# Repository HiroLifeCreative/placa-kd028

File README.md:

# Placa KD028 v1.0 — Proyecto KiCad (INICIO, no fabricación)

Abrir en KiCad 8: `placa-kd028.kicad_pro` (o abrir `placa-kd028.kicad_pcb` y
`placa-kd028.kicad_sch` desde KiCad).

Contenido:
- Esquemático v1.0: U1 ESP32-S3-WROOM-1-N8R8, U2 buck 5V->3.3V 3A,
  U3 boost LED ~17.5V, J1 FPC 40 pines ST7701S, U5 BH1750, U6 TMP117,
  USB, ESD, BOOT/RESET. Conexiones por etiquetas globales de red.
- PCB: contorno redondo Ø70 mm (Edge.Cuts), 1.2 mm, 4 capas
  (F.Cu, In1.Cu, In2.Cu, B.Cu), huellas colocadas según el layout v1.0,
  pistas iniciales RGB (0.25 mm), alimentación 1.5 mm y LED 1.0 mm,
  3 agujeros M3 Ø3.2 mm a radio 31 mm.

Pasos en KiCad:
1. Schematic Editor: Tools > Electrical Rules Check (ERC) — corregir
   pines sin conectar.
2. PCB Editor: Tools > Design Rules Check (DRC), y comprobar
   ancho de pista de alimentación y separación del boost.
3. Vista 3D (Alt+3) para revisar altura de componentes por detrás.

BLOQUEO ANTES DE FABRICAR (no saltar):
- Confirmar hoja de datos / plano del KD028WXFPD075: pinout exacto
  del FPC de 40 pines y cadena de LEDs. El J1 de este proyecto usa
  el pinout genérico ST7701S de la familia; si el KD028 difiere,
  hay que corregir J1 y el ruteo RGB/SPI antes de generar Gerbers.
- Medir en el coche: distancia entre centros de los 2 agujeros del
  emblema, diámetros y grosor de tapa (para la placa trasera, no
  para esta PCB, que ya es Ø70 mm).
- Solo entonces: File > Fabrication Outputs > Gerbers + Drill,
  y revisión DFM del fabricante.

Nada comprado ni fabricado con este proyecto todavía.

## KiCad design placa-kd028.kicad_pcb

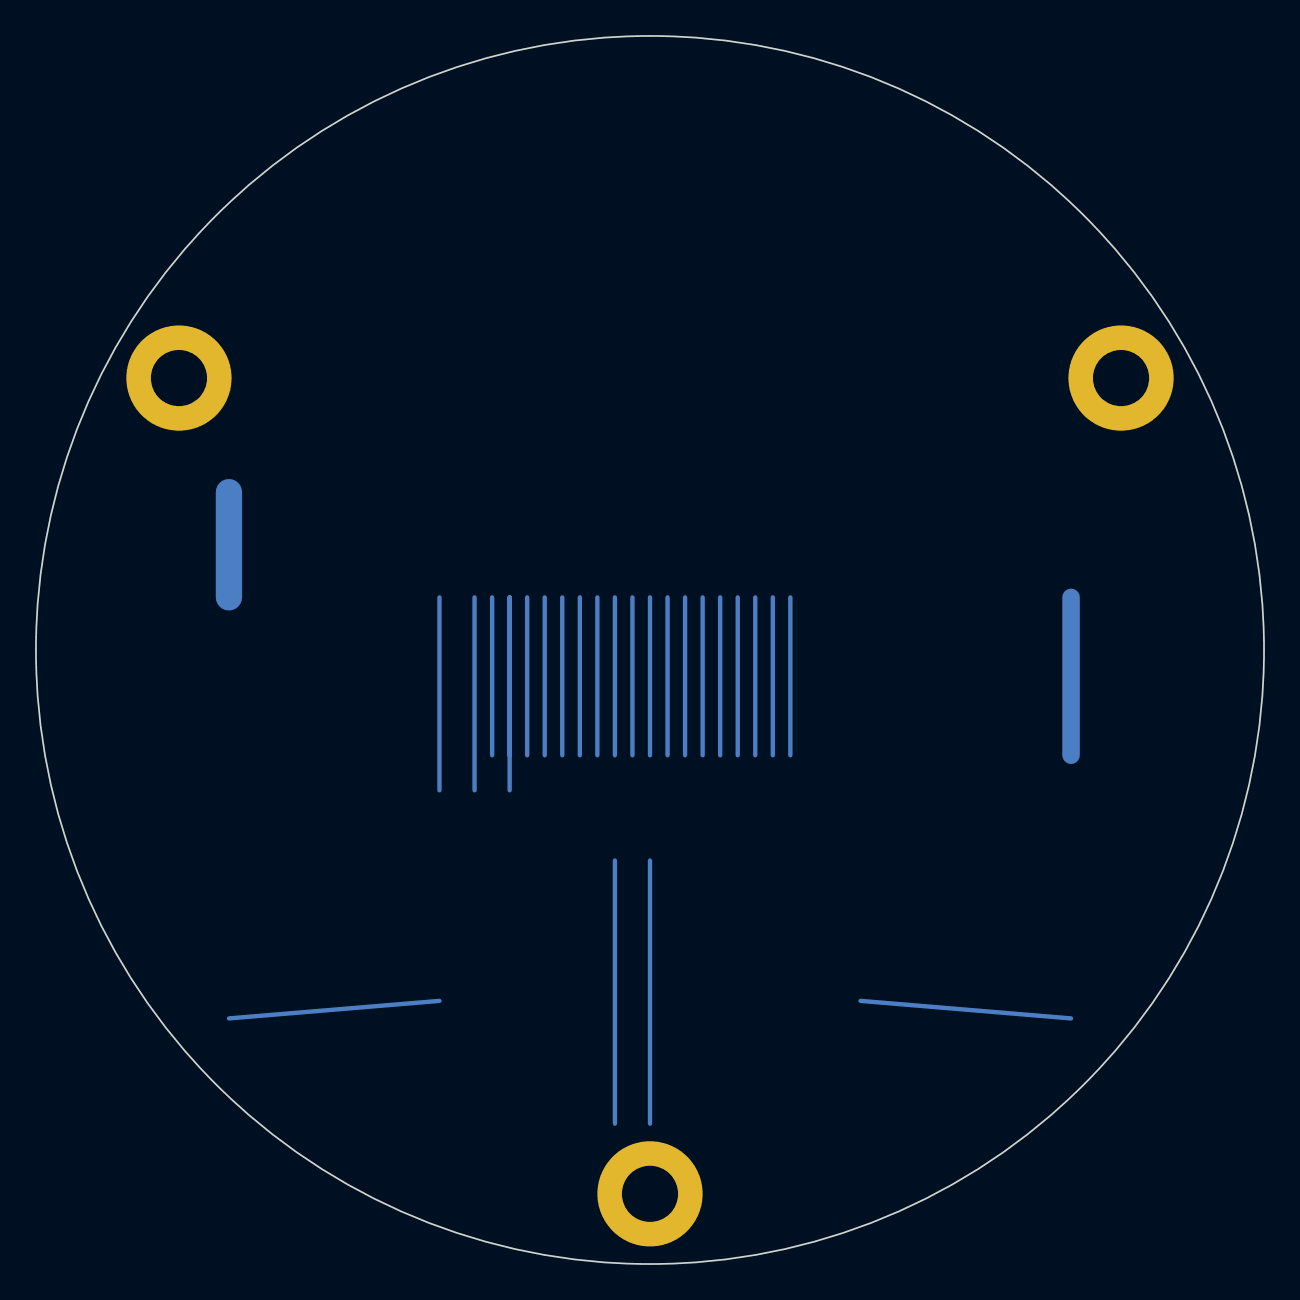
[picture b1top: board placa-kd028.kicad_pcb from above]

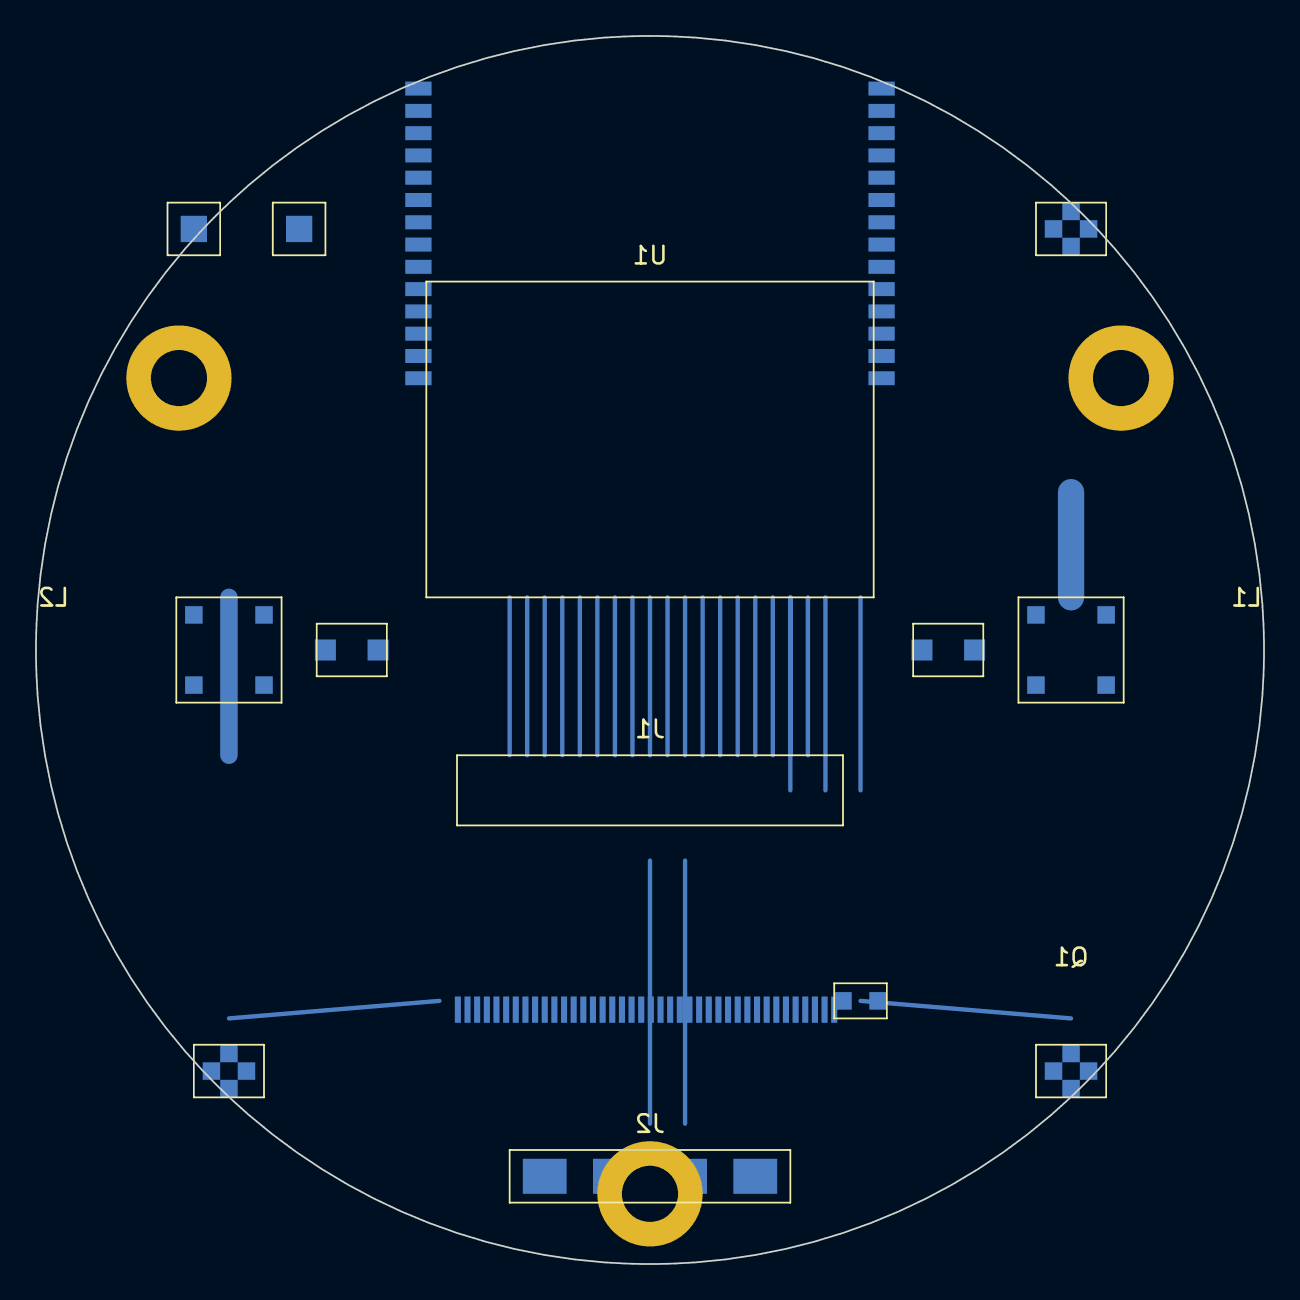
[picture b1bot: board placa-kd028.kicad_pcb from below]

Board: 4 copper layers, 70.0 x 70.0 mm, 16 parts (13 on the bottom side), 28 nets.

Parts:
H1, H2, H3: MountingHole
J1: FPC-40-0.5mm-ST7701S
J2: USB-PADS
L1: IND-2.2uH
L2: IND-BOOST
Q1: MOSFET-PANEL-EN
SW1: BOOT
SW2: RESET
U1: ESP32-S3-WROOM-1-N8R8
U2: MP2315S-BUCK-3A
U3: TPS61165-BOOST-LED
U4: USBLC6-2-ESD
U5: BH1750
U6: TMP117

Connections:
GND: H1.1, H2.1, H3.1, J1.3, J1.27, J1.28, J1.29, J1.30, J1.31, J1.32, J1.33, J1.34, J1.35, J1.36, J1.37, J1.38, J1.39, J1.40, J2.4, SW1.1, SW2.1, U1.1, U1.6, U1.11, U2.3, U3.3, U4.3, U5.4, U6.4
I2C_SCL: U1.10, U5.3, U6.3
I2C_SDA: U1.9, U5.2, U6.2
LED_PLUS: J1.1, L2.2, U3.2
PANEL_EN: Q1.2, U1.13
PANEL_RESET: J1.5, U1.12
RGB_B1: J1.10, U1.2
RGB_B2: J1.11, U1.15
RGB_B3: J1.12, U1.16
RGB_B4: J1.13, U1.17
RGB_B5: J1.14, U1.18
RGB_G0: J1.15, U1.3
RGB_G1: J1.16, U1.19
RGB_G2: J1.17, U1.20
RGB_G3: J1.18, U1.21
RGB_G4: J1.19, U1.22
RGB_G5: J1.20, U1.23
RGB_R0: J1.21, U1.24
RGB_R1: J1.22, U1.25
RGB_R2: J1.23, U1.26
RGB_R3: J1.24, U1.27
RGB_R4: J1.25, U1.28
SPI_CS: J1.8, U1.4
SPI_SCL: J1.7, U1.5
USB_DM: J2.2, U1.7, U4.1
USB_DP: J2.3, U1.8, U4.2
V3V3: J1.4, L1.1, L1.2, Q1.1, U1.14, U2.2, U2.4, U5.1, U6.1
VBUS_5V: J2.1, L2.1, U2.1, U3.1, U4.4
